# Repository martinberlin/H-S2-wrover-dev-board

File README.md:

## An open source S2-WROVER board with minimun components and DFU USB

H stands for Hardware. **IMPORTANT NOTE: Please do not intend to build this PCB. **
It was my first EPDiy like controller and has a lot of newbie defects. Including selecting no REAL TIME pins from the IO MUX to use as Clock and Start pulse for I2S. As is won't work, and in the next months, I won't have time to play with electronics.

Initial dimensions:
99x50mm

Note: Previews are taken from the [v1 branch](https://github.com/martinberlin/H-S2-wrover-dev-board/tree/v1).

This board aims to be the simplest possible configuration to have a breakout PCB to start developing something with Espressif S2.
The minimun requirements are:

- Lipo charger and a 2 leds indicator (charge, full)
- All GPIOs exposed
- No Serial-to-UART. Only dfu USB, please check this [blog post from Espressif](https://blog.espressif.com/dfu-using-the-native-usb-on-esp32-s2-for-flashing-the-firmware-b2c4af3335f1)
- Only 2 layer (Cheaper to fabricate)
- **Important** For simplicity this test board has no Auto-Reset circuit (Check [epdiy Schematic](https://github.com/martinberlin/H-S2-wrover-dev-board/tree/epd-v1/Schematic))

## EPDiy S2 PCB

In the **epd-v1** branch it's my first attempt to design an EPDiy V6 clone. This is still on fabrication and as the prototype Revision 1.1 still need a lot of tests and adjustments.
This will be probably merged in master once is tested and working as expected. Being my first somehow complex ESP32S2 boards I will for sure 

Both boards Still a work in progress, no Gerbers, no pick-place and no production files at all. It needs testing before everything can be published.

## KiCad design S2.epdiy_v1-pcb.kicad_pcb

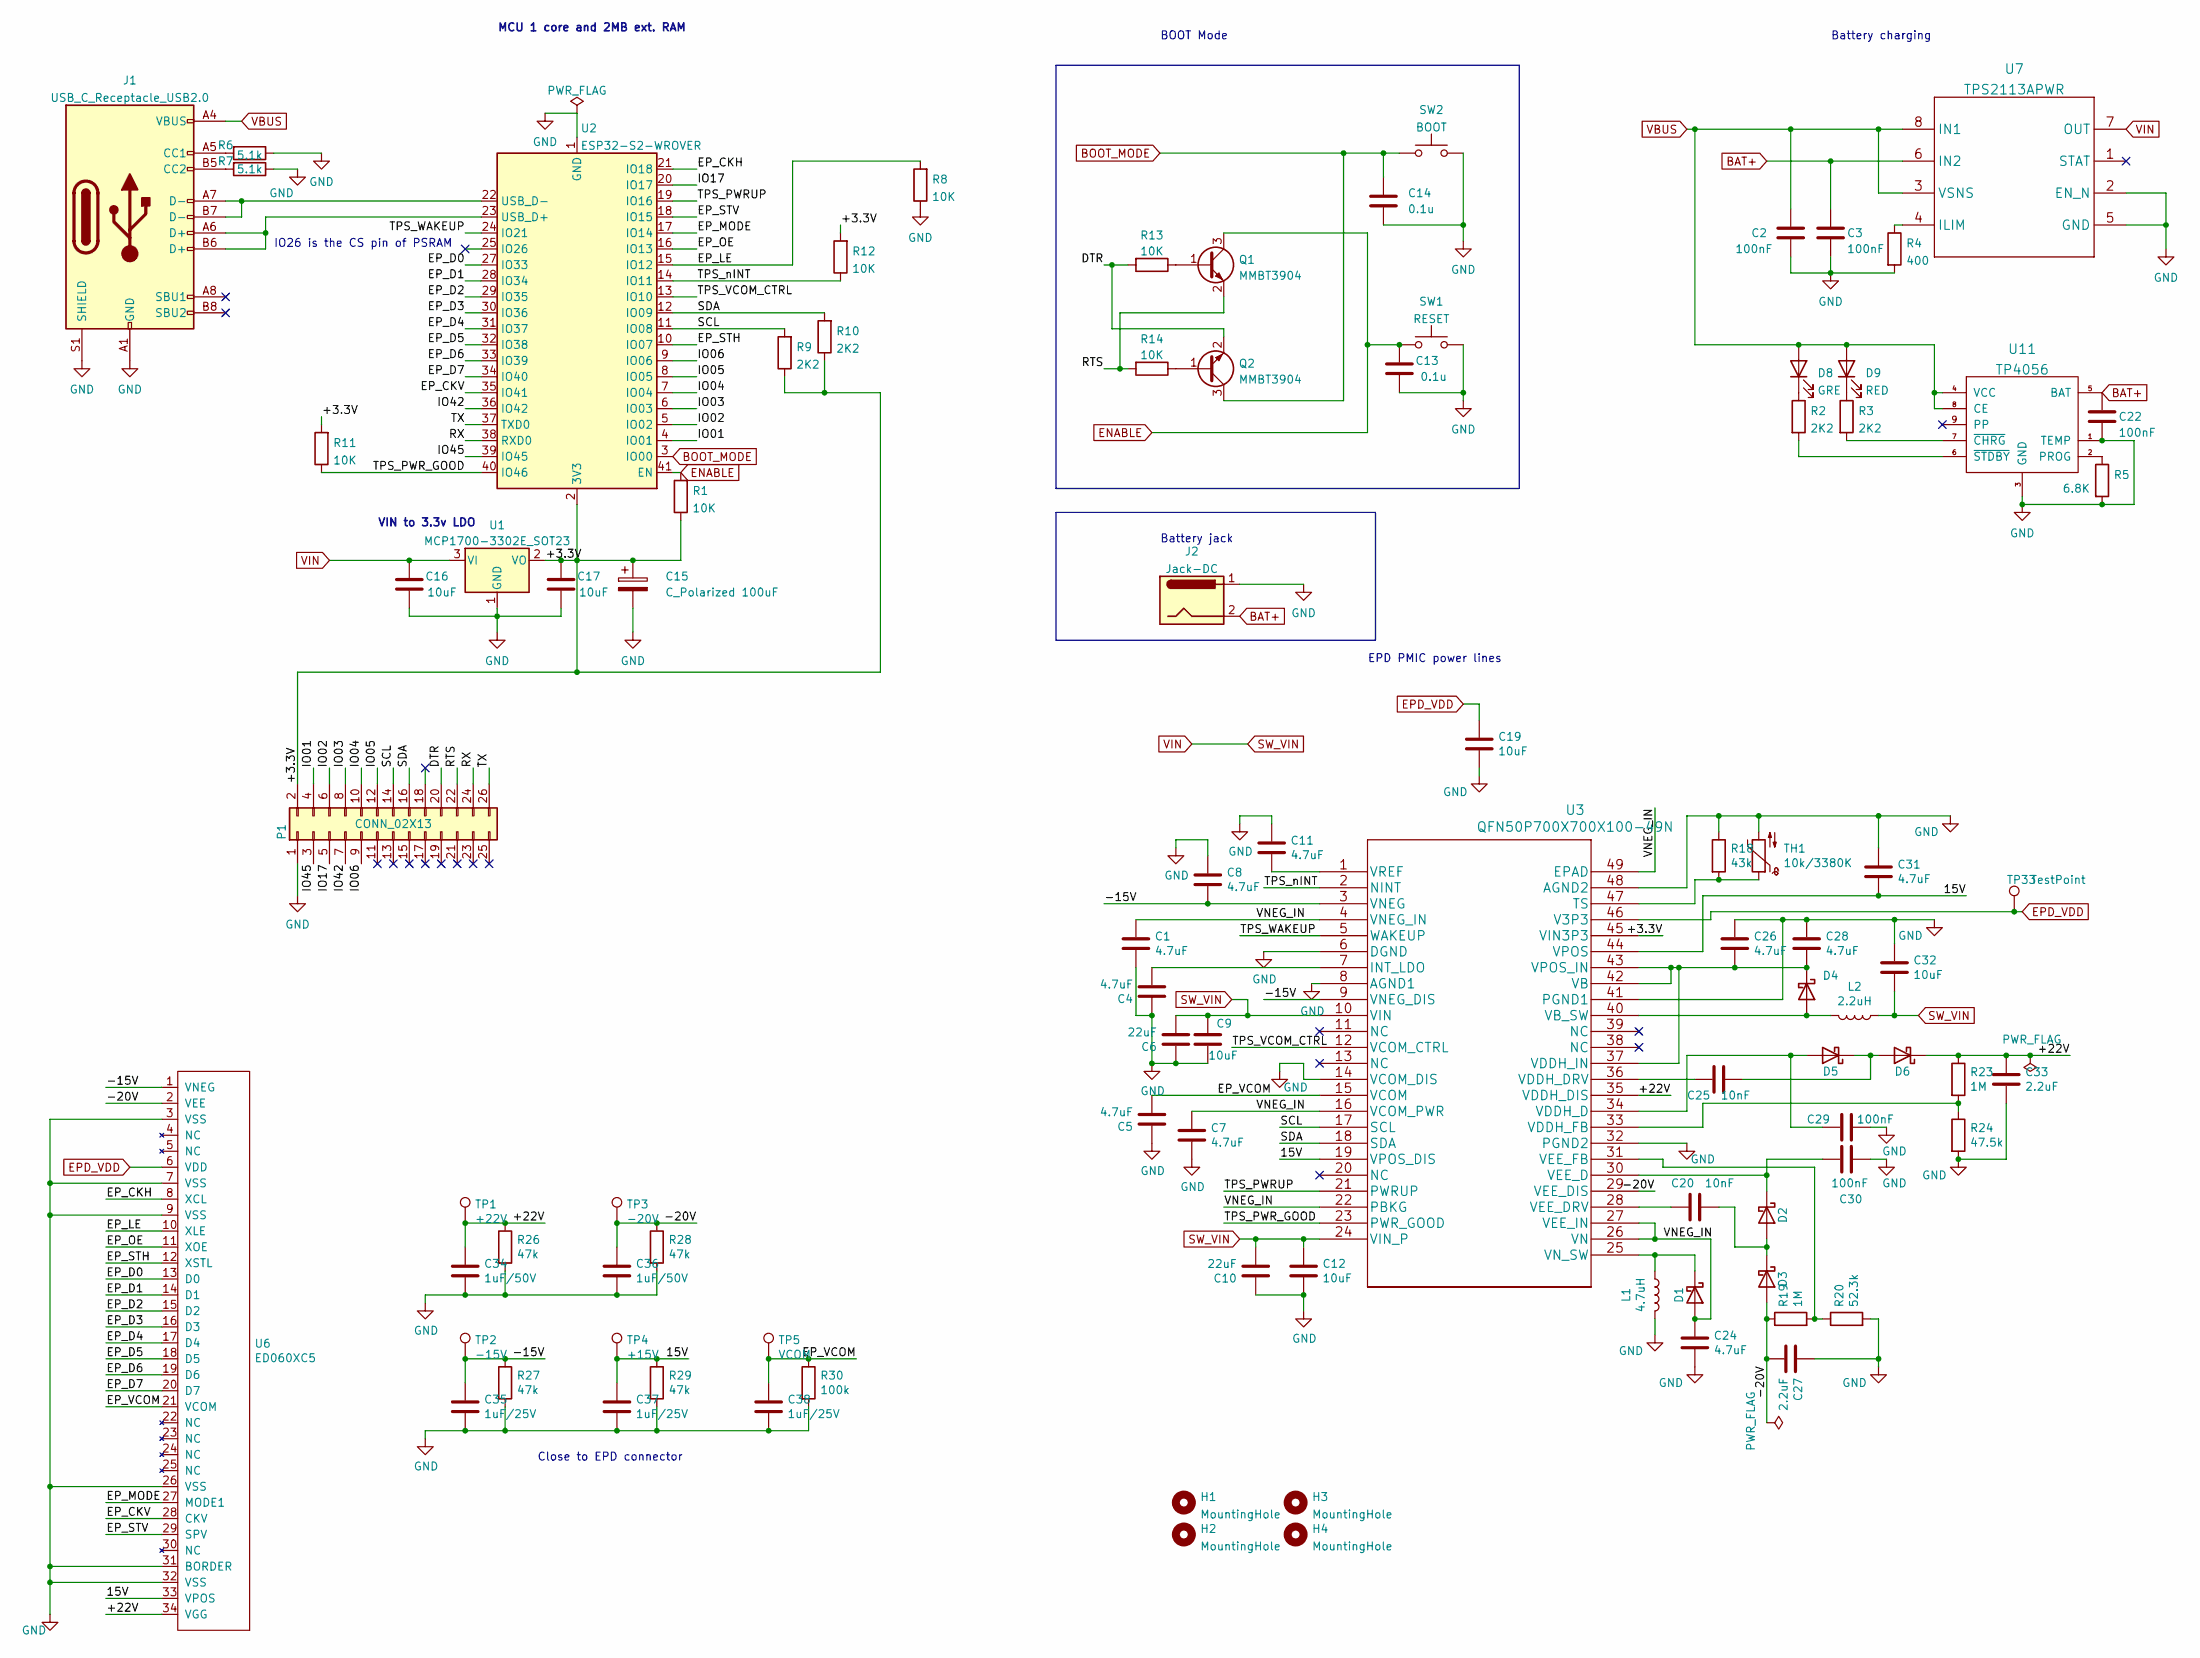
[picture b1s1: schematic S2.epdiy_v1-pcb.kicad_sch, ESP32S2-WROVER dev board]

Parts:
C1, C4, C5, C7, C8, C11, C24, C26, C28, C31: 4.7uF; C_0805_2012Metric; LCSC C1779
C2, C3, C22, C29, C30: 100nF; C_0805_2012Metric; LCSC C49678
C6, C10: 22uF; C_0805_2012Metric; LCSC C45783
C9, C12, C16, C17, C32: 10uF; C_0805_2012Metric; LCSC C15850
C13: 0.1u; C_0805_2012Metric
C14: 0.1u; C_0805_2012Metric; LCSC C28323
C15: C_Polarized 100uF; CP_EIA-3528-21_Kemet-B; LCSC C129289
C19: 10uF; C_0805_2012Metric; LCSC C19702
C20, C25: 10nF; C_0805_2012Metric; LCSC C1710
C27, C33: 2.2uF; C_0805_2012Metric; LCSC C49217
C34, C36: 1uF/50V; C_1206_3216Metric; LCSC C1848
C35, C37, C38: 1uF/25V; C_0805_2012Metric; LCSC C28323
D1, D2, D3, D4, D5, D6: MBR0540; D_SOD-123; LCSC C21353
D8: GRE; LED_0805_2012Metric; LCSC C2297
D9: RED; LED_0805_2012Metric; LCSC C84256
H1, H2, H3, H4: MountingHole; MountingHole_2.5mm
J1: USB_C_Receptacle_USB2.0; USB_C_Receptacle_HRO_TYPE-C-31-M-12; LCSC C165948
J2: Jack-DC; JST_EH_S2B-EH_1x02_P2.50mm_Horizontal
L1: 4.7uH; L_Taiyo-Yuden_NR-50xx_HandSoldering; LCSC C222947
L2: 2.2uH; L_Taiyo-Yuden_NR-40xx_HandSoldering; LCSC C92959
P1: CONN_02X13; PinHeader_2x13_P2.54mm_Vertical
Q1, Q2: MMBT3904; SOT-23; LCSC C20526
R1, R8, R11, R13: 10K; R_0603_1608Metric; LCSC C25804
R2, R3: 2K2; R_0603_1608Metric; LCSC C25804
R4: 400; R_0603_1608Metric; LCSC C23151
R5: 6.8K; R_0603_1608Metric; LCSC C23212
R6, R7: 5.1k; R_0603_1608Metric; LCSC C25803
R9, R10: 2K2; R_0603_1608Metric; LCSC C4190
R12, R14: 10K; R_0603_1608Metric; LCSC C25197
R18: 43k; R_0603_1608Metric; LCSC C23172
R19, R23: 1M; R_0603_1608Metric; LCSC C22935
R20: 52.3k; R_0603_1608Metric; LCSC C23196
R24: 47.5k; R_0603_1608Metric; LCSC C25819
R26, R27, R28, R29: 47k; R_0603_1608Metric; LCSC C25819
R30: 100k; R_0603_1608Metric; LCSC C25803
SW1: RESET; Alps_SKRK
SW2: BOOT; Alps_SKRK; LCSC C202388
TH1: 10k/3380K; R_0603_1608Metric; LCSC C76589
TP1: +22V; TestPoint_Pad_D2.5mm
TP2: -15V; TestPoint_Pad_D2.5mm
TP3: -20V; TestPoint_Pad_D2.5mm
TP4: +15V; TestPoint_Pad_D2.5mm
TP5: VCOM; TestPoint_Pad_D2.5mm
TP33: TestPoint; TestPoint_Pad_2.0x2.0mm
U1: MCP1700-3302E_SOT23; SOT-23; LCSC C39051
U2: ESP32-S2-WROVER; LCSC C701333
U3: QFN50P700X700X100-49N; TPS65185RGZR_700X700X100-49N; LCSC C139292
U6: ED060XC5; X05A20H34G; LCSC C528053
U7: TPS2113APWR; TPS2113APW; LCSC C130052
U11: TP4056; TP4056_SOP-8-PP; LCSC C16581

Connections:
/15V: C31.2, C37.1, R29.1, TP4.1, U3.19 (VPOS_DIS), U3.44 (VPOS), U6.33 (VPOS)
/+3.3V: C15.1, C17.1, P1.2, R1.1, R9.1, R10.1, R11.2, R12.2, U1.2 (VO), U2.2 (3V3), U3.45 (VIN3P3)
/+22V: C33.1, C34.1, D6.1 (K), R23.1, R26.1, TP1.1, U3.35 (VDDH_DIS), U6.34 (VGG)
/-15V: C8.2, C35.1, R27.1, TP2.1, U3.3 (VNEG), U3.9 (VNEG_DIS), U6.1 (VNEG)
/-20V: C27.2, C36.1, D3.2 (A), R19.1, R28.1, TP3.1, U3.29 (VEE_DIS), U6.2 (VEE)
/DTR: P1.20, Q2.2 (E), R13.2
/EP_CKH: U2.21 (IO18), U6.8 (XCL)
/EP_CKV: U2.35 (IO41), U6.28 (CKV)
/EP_D0: U2.27 (IO33), U6.13 (D0)
/EP_D1: U2.28 (IO34), U6.14 (D1)
/EP_D2: U2.29 (IO35), U6.15 (D2)
/EP_D3: U2.30 (IO36), U6.16 (D3)
/EP_D4: U2.31 (IO37), U6.17 (D4)
/EP_D5: U2.32 (IO38), U6.18 (D5)
/EP_D6: U2.33 (IO39), U6.19 (D6)
/EP_D7: U2.34 (IO40), U6.20 (D7)
/EP_LE: R8.2, U2.15 (IO12), U6.10 (XLE)
/EP_MODE: U2.17 (IO14), U6.27 (MODE1)
/EP_OE: U2.16 (IO13), U6.11 (XOE)
/EP_STH: U2.10 (IO07), U6.12 (XSTL)
/EP_STV: U2.18 (IO15), U6.29 (SPV)
/EP_VCOM: C5.2, C38.1, R30.1, TP5.1, U3.15 (VCOM), U6.21 (VCOM)
/IO01: P1.4, U2.4 (IO01)
/IO02: P1.6, U2.5 (IO02)
/IO03: P1.8, U2.6 (IO03)
/IO04: P1.10, U2.7 (IO04)
/IO05: P1.12, U2.8 (IO05)
/IO06: P1.9, U2.9 (IO06)
/IO17: P1.5, U2.20 (IO17)
/IO42: P1.7, U2.36 (IO42)
/IO45: P1.3, U2.39 (IO45)
/RTS: P1.22, Q1.2 (E), R14.2
/RX: P1.24, U2.38 (RXD0)
/SCL: P1.14, R9.2, U2.11 (IO08), U3.17 (SCL)
/SDA: P1.16, R10.2, U2.12 (IO09), U3.18 (SDA)
/TPS_PWRUP: U2.19 (IO16), U3.21 (PWRUP)
/TPS_PWR_GOOD: R11.1, U2.40 (IO46), U3.23 (PWR_GOOD)
/TPS_VCOM_CTRL: U2.13 (IO10), U3.12 (VCOM_CTRL)
/TPS_WAKEUP: U2.24 (IO21), U3.5 (WAKEUP)
/TPS_nINT: R12.1, U2.14 (IO11), U3.2 (NINT)
/TX: P1.26, U2.37 (TXD0)
/VNEG_IN: C1.1, C7.1, C24.1, D1.2 (A), U3.4 (VNEG_IN), U3.16 (VCOM_PWR), U3.22 (PBKG), U3.26 (VN), U3.27 (VEE_IN), U3.49 (EPAD)
BAT+: C3.2, C22.2, J2.2, U7.6 (IN2), U11.5 (BAT)
BOOT_MODE: C14.2, Q2.3 (C), SW2.1, U2.3 (IO00)
ENABLE: C13.1, Q1.3 (C), R1.2, SW1.1, U2.41 (EN)
EPD_VDD: C19.1, TP33.1, U3.46 (V3P3), U6.6 (VDD)
GND: C1.2, C2.1, C3.1, C4.1, C5.1, C6.1, C7.2, C8.1, C9.2, C10.1, C11.1, C12.2, C13.2, C14.1, C15.2, C16.2, C17.2, C19.2, C22.1, C24.2, C26.1, C27.1, C28.1, C29.1, C30.2, C31.1, C32.1, C33.2, C34.2, C35.2, C36.2, C37.2, C38.2, J1.A1 (GND), J1.A12 (GND), J1.B1 (GND), J1.B12 (GND), J1.S1 (SHIELD), J2.1, L1.2, P1.1, R4.2, R5.2, R6.1, R7.1, R8.1, R18.1, R20.2, R24.2, R26.2, R27.2, R28.2, R29.2, R30.2, SW1.2, SW2.2, TH1.2, U1.1 (GND), U2.1 (GND), U2.26 (GND), U2.42 (GND), U2.43 (GND), U3.6 (DGND), U3.8 (AGND1), U3.14 (VCOM_DIS), U3.32 (PGND2), U3.41 (PGND1), U3.48 (AGND2), U6.3 (VSS), U6.7 (VSS), U6.9 (VSS), U6.26 (VSS), U6.31 (BORDER), U6.32 (VSS), U7.2 (EN_N), U7.5 (GND), U11.1 (TEMP), U11.3 (GND)
unnamed: C4.2, U3.7 (INT_LDO)
unnamed: C11.2, U3.1 (VREF)
unnamed: C20.1, D2.2 (A), D3.1 (K)
unnamed: C20.2, U3.28 (VEE_DRV)
unnamed: C25.1, D5.1 (K), D6.2 (A)
unnamed: C25.2, U3.36 (VDDH_DRV)
unnamed: C26.2, C28.2, D4.1 (K), U3.37 (VDDH_IN), U3.42 (VB), U3.43 (VPOS_IN)
unnamed: C29.2, D5.2 (A), U3.34 (VDDH_D)
unnamed: C30.1, D2.1 (K), U3.30 (VEE_D)
unnamed: D1.1 (K), L1.1, U3.25 (VN_SW)
unnamed: D4.2 (A), L2.2, U3.40 (VB_SW)
unnamed: D8.1 (K), R2.1
unnamed: D9.1 (K), R3.1
unnamed: J1.A5 (CC1), R6.2
unnamed: J1.A6 (D+), J1.B6 (D+), U2.23 (USB_D+)
unnamed: J1.A7 (D-), J1.B7 (D-), U2.22 (USB_D-)
unnamed: J1.B5 (CC2), R7.2
unnamed: Q1.1 (B), R13.1
unnamed: Q2.1 (B), R14.1
unnamed: R2.2, U11.6 (~STDBY)
unnamed: R3.2, U11.7 (~CHRG)
unnamed: R4.1, U7.4 (ILIM)
unnamed: R5.1, U11.2 (PROG)
unnamed: R18.2, TH1.1, U3.47 (TS)
unnamed: R19.2, R20.1, U3.31 (VEE_FB)
unnamed: R23.2, R24.1, U3.33 (VDDH_FB)
SW_VIN: C6.2, C9.1, C10.2, C12.1, C16.1, C32.2, L2.1, U1.3 (VI), U3.10 (VIN), U3.24 (VIN_P), U7.7 (OUT)
VBUS: C2.2, D8.2 (A), D9.2 (A), J1.A4 (VBUS), J1.A9 (VBUS), J1.B4 (VBUS), J1.B9 (VBUS), U7.3 (VSNS), U7.8 (IN1), U11.4 (VCC), U11.8 (CE)

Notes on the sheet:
Battery charging
Battery jack
Close to EPD connector
BOOT Mode
MCU 1 core and 2MB ext. RAM
IO26 is the CS pin of PSRAM
EPD PMIC power lines
VIN to 3.3v LDO

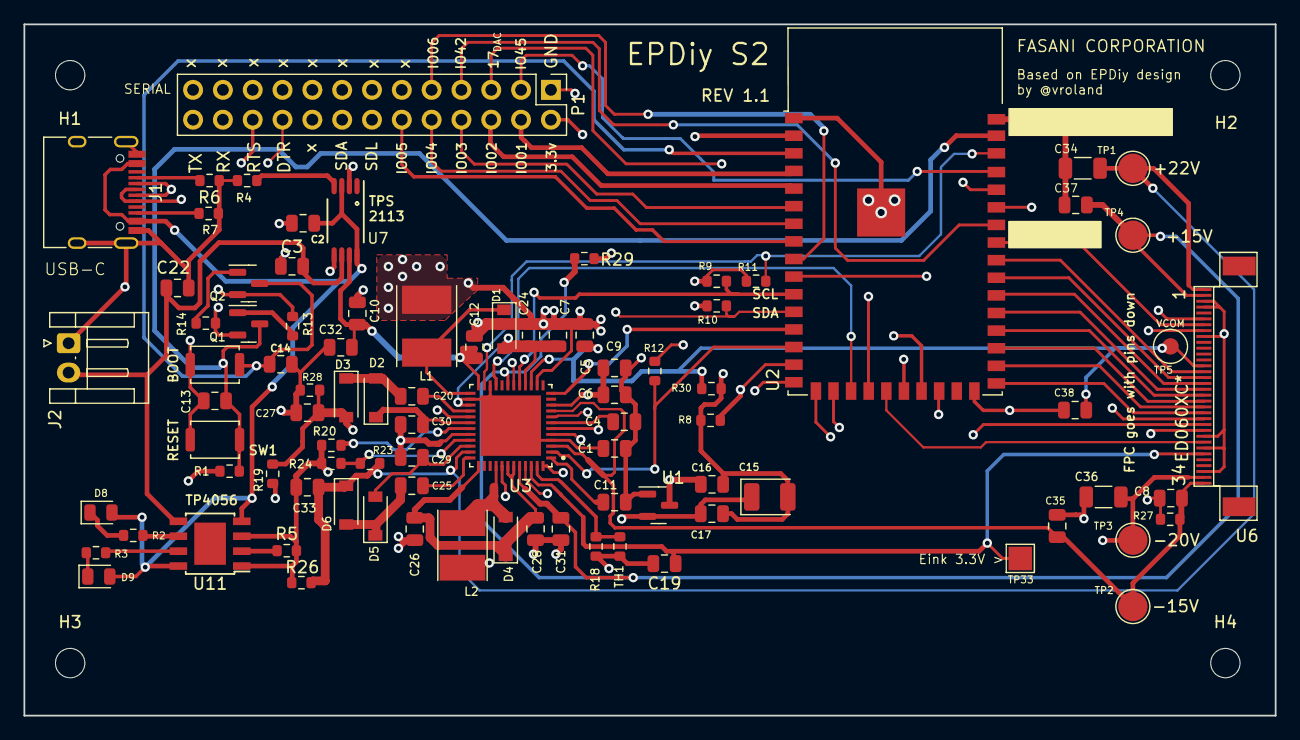
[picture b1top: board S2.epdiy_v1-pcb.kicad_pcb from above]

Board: 4 copper layers, 106.6 x 58.9 mm, 93 parts (0 on the bottom side), 75 nets.

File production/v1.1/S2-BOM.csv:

"Id";"Designator";"Package";"Quantity";"Designation";"Supplier and ref";
1;"R14,R13,R12,R8,R11,R1";"R_0603_1608Metric";6;"10K";;;
2;"Q2,Q1";"SOT-23";2;"MMBT3904";;;
3;"C15";"CP_EIA-3528-21_Kemet-B";1;"C_Polarized 100uF";;;
4;"C34,C36";"C_1206_3216Metric";2;"1uF/50V";;;
5;"D8";"LED_0805_2012Metric";1;"GRE";;;
6;"C31,C5,C24,C1,C26,C28,C11,C7,C8,C4";"C_0805_2012Metric";10;"4.7uF";;;
7;"U7";"TPS2113APW";1;"TPS2113APWR";;;
8;"TP33";"TestPoint_Pad_2.0x2.0mm";1;"TestPoint";;;
9;"R10,R3,R2,R9";"R_0603_1608Metric";4;"2K2";;;
10;"TP1";"TestPoint_Pad_D2.5mm";1;"+22V";;;
11;"C16,C9,C12,C19,C32,C17";"C_0805_2012Metric";6;"10uF";;;
12;"SW2";"Alps_SKRK";1;"BOOT";;;
13;"R5";"R_0603_1608Metric";1;"6.8K";;;
14;"C10,C6";"C_0805_2012Metric";2;"22uF";;;
15;"D2,D1,D3,D4,D6,D5";"D_SOD-123";6;"MBR0540";;;
16;"C3,C22,C29,C2,C30";"C_0805_2012Metric";5;"100nF";;;
17;"R24";"R_0603_1608Metric";1;"47.5k";;;
18;"C14,C13";"C_0805_2012Metric";2;"0.1u";;;
19;"TP3";"TestPoint_Pad_D2.5mm";1;"-20V";;;
20;"R30";"R_0603_1608Metric";1;"100k";;;
21;"H1,H3,H4,H2";"MountingHole_2.5mm";4;"MountingHole";;;
22;"R4";"R_0603_1608Metric";1;"400";;;
23;"R20";"R_0603_1608Metric";1;"52.3k";;;
24;"R19,R23";"R_0603_1608Metric";2;"1M";;;
25;"U3";"TPS65185RGZR_700X700X100-49N";1;"QFN50P700X700X100-49N";;;
26;"C27,C33";"C_0805_2012Metric";2;"2.2uF";;;
27;"C20,C25";"C_0805_2012Metric";2;"10nF";;;
28;"J2";"JST_EH_S2B-EH_1x02_P2.50mm_Horizontal";1;"Jack-DC";;;
29;"R28,R29,R27,R26";"R_0603_1608Metric";4;"47k";;;
30;"L1";"L_Taiyo-Yuden_NR-50xx_HandSoldering";1;"4.7uH";;;
31;"TP4";"TestPoint_Pad_D2.5mm";1;"+15V";;;
32;"R7,R6";"R_0603_1608Metric";2;"5.1k";;;
33;"U6";"X05A20H34G";1;"ED060XC5";;;
34;"C38,C35,C37";"C_0805_2012Metric";3;"1uF/25V";;;
35;"R18";"R_0603_1608Metric";1;"43k";;;
36;"U2";"ESP32-S2-WROVER";1;"ESP32-S2-WROVER";;;
37;"TH1";"R_0603_1608Metric";1;"10k/3380K";;;
38;"P1";"PinHeader_2x13_P2.54mm_Vertical";1;"CONN_02X13";;;
39;"U1";"SOT-23";1;"MCP1700-3302E_SOT23";;;
40;"D9";"LED_0805_2012Metric";1;"RED";;;
41;"U11";"TP4056_SOP-8-PP";1;"TP4056";;;
42;"SW1";"Alps_SKRK";1;"RESET";;;
43;"J1";"USB_C_Receptacle_HRO_TYPE-C-31-M-12";1;"USB_C_Receptacle_USB2.0";;;
44;"L2";"L_Taiyo-Yuden_NR-40xx_HandSoldering";1;"2.2uH";;;
45;"TP5";"TestPoint_Pad_D2.5mm";1;"VCOM";;;
46;"TP2";"TestPoint_Pad_D2.5mm";1;"-15V";;;

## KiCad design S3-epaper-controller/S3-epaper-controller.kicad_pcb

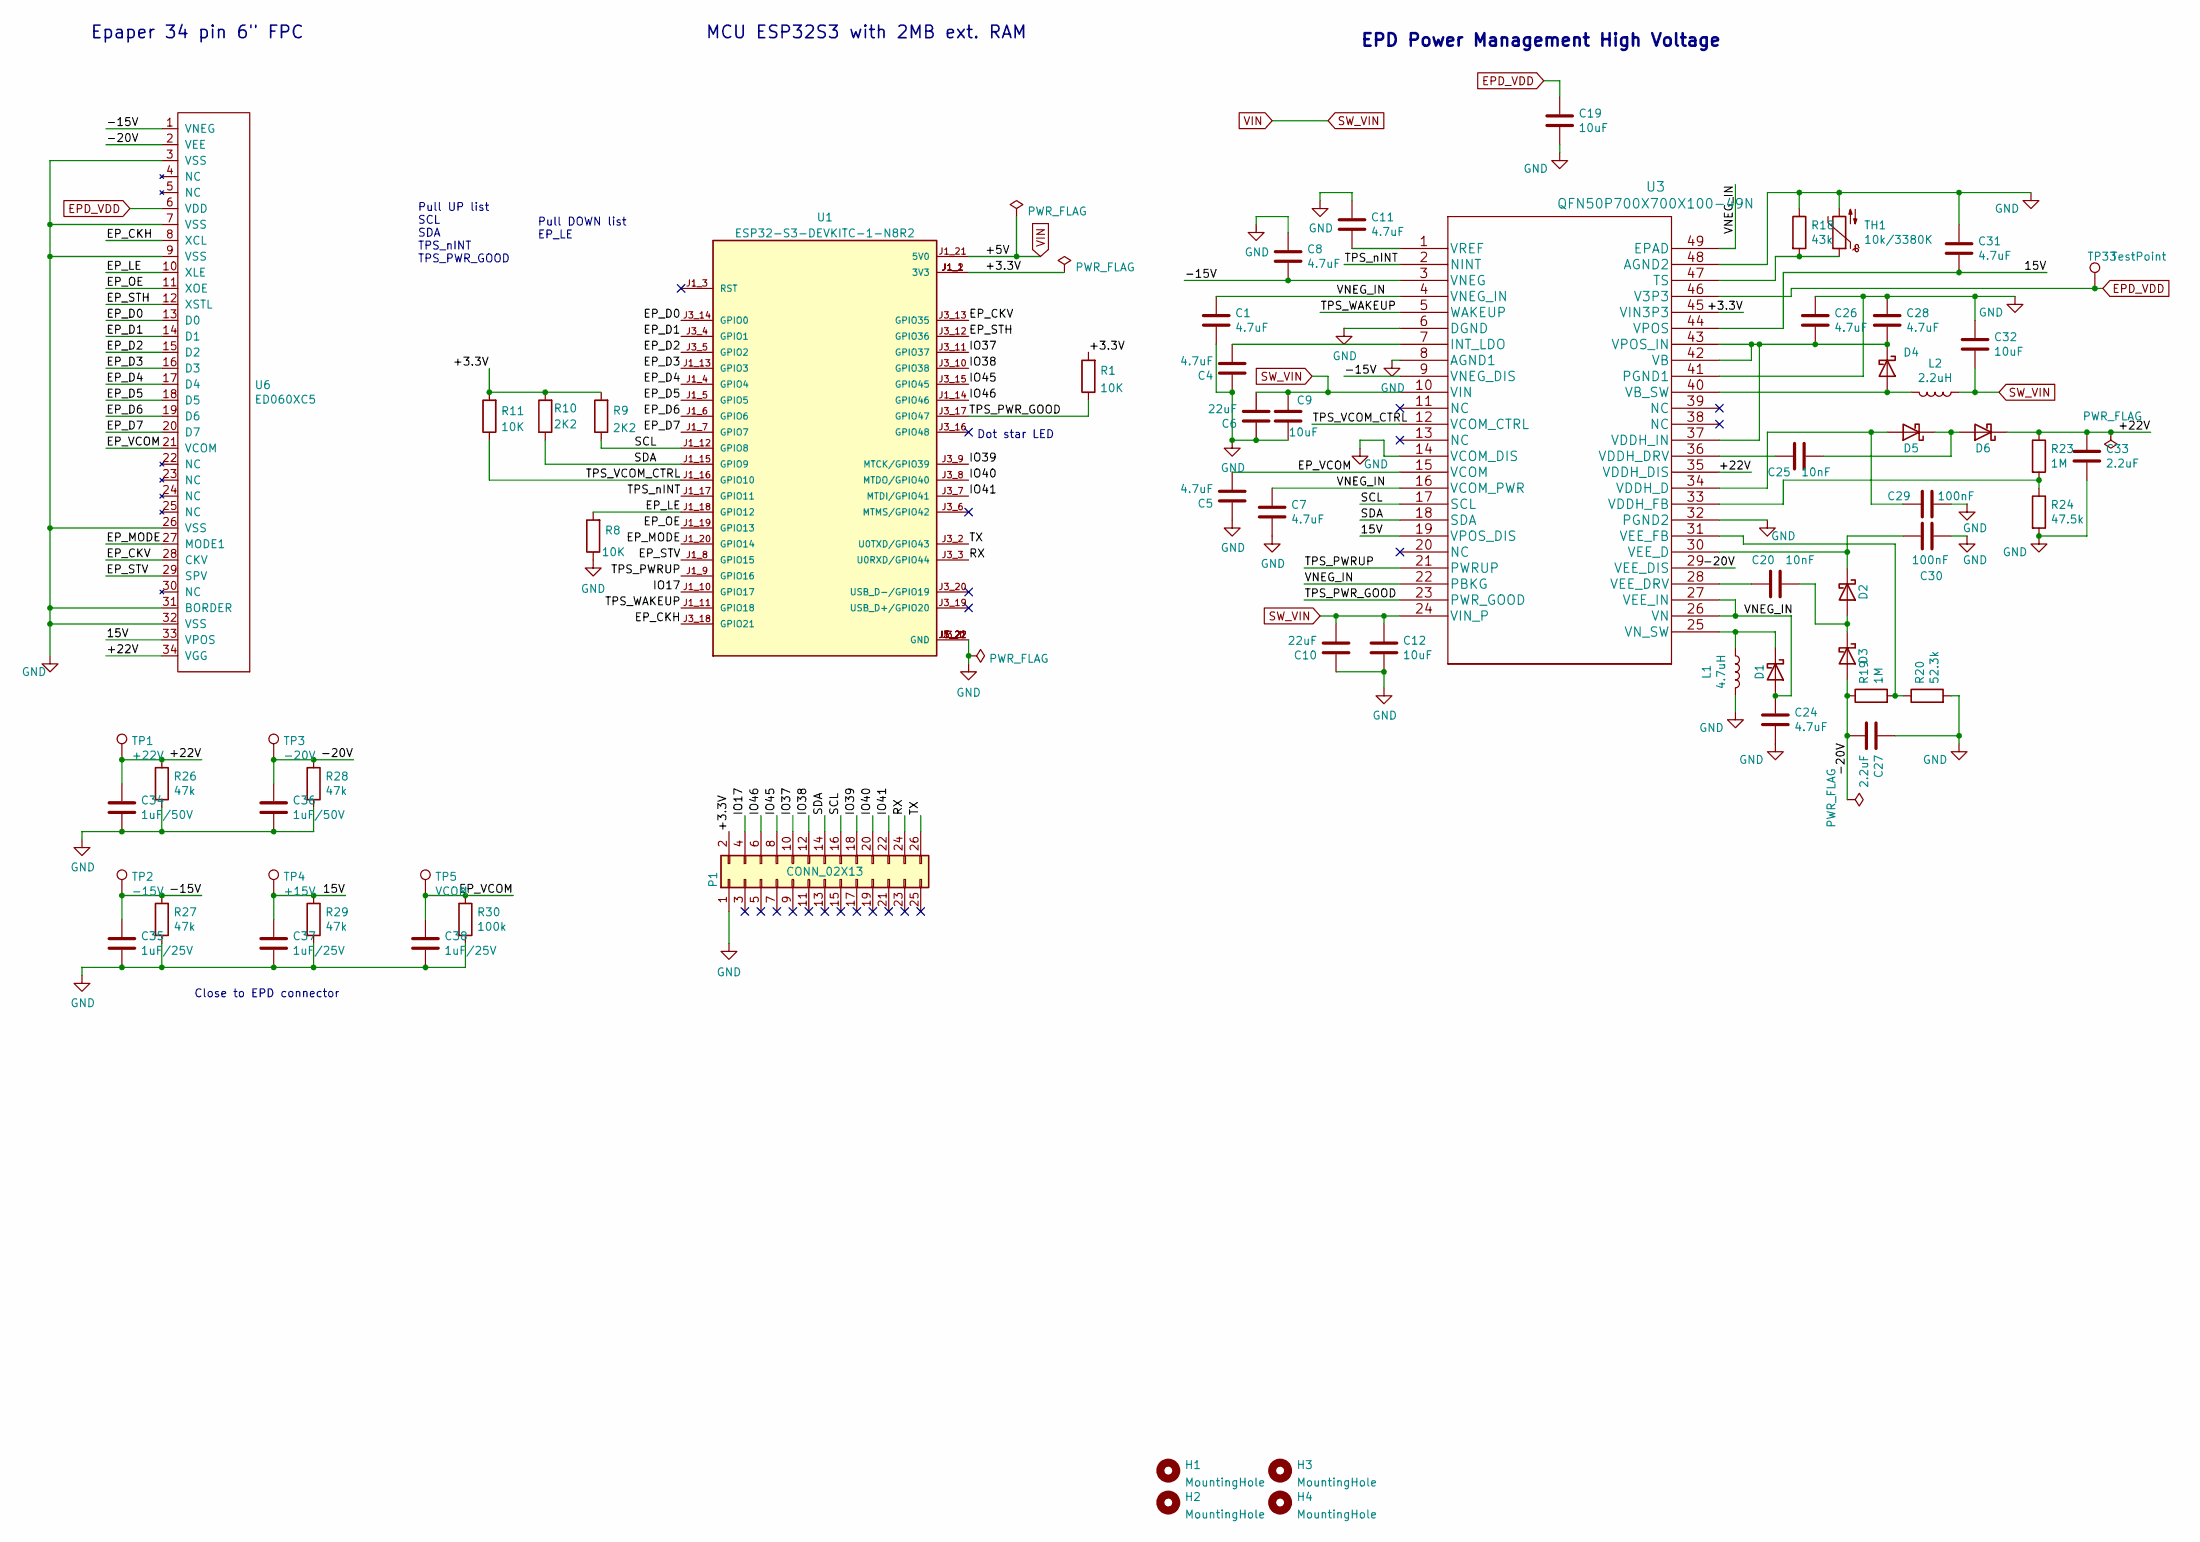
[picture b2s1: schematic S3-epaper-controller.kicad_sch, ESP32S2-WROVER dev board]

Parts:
C1, C4, C5, C7, C8, C11, C24, C26, C28, C31: 4.7uF; C_0805_2012Metric; LCSC C1779
C6, C10: 22uF; C_0805_2012Metric; LCSC C45783
C9, C12, C32: 10uF; C_0805_2012Metric; LCSC C15850
C19: 10uF; C_0805_2012Metric; LCSC C19702
C20, C25: 10nF; C_0805_2012Metric; LCSC C1710
C27, C33: 2.2uF; C_0805_2012Metric; LCSC C49217
C29, C30: 100nF; C_0805_2012Metric; LCSC C49678
C34, C36: 1uF/50V; C_1206_3216Metric; LCSC C1848
C35, C37, C38: 1uF/25V; C_0805_2012Metric; LCSC C28323
D1, D2, D3, D4, D5, D6: MBR0540; D_SOD-123; LCSC C21353
H1, H2, H3, H4: MountingHole; MountingHole_2.5mm
L1: 4.7uH; L_Taiyo-Yuden_NR-50xx_HandSoldering; LCSC C222947
L2: 2.2uH; L_Taiyo-Yuden_NR-40xx_HandSoldering; LCSC C92959
P1: CONN_02X13; PinHeader_2x13_P2.54mm_Vertical
R1, R8, R11: 10K; R_0603_1608Metric; LCSC C25197
R9, R10: 2K2; R_0603_1608Metric; LCSC C4190
R18: 43k; R_0603_1608Metric; LCSC C23172
R19, R23: 1M; R_0603_1608Metric; LCSC C22935
R20: 52.3k; R_0603_1608Metric; LCSC C23196
R24: 47.5k; R_0603_1608Metric; LCSC C25819
R26, R27, R28, R29: 47k; R_0603_1608Metric; LCSC C25819
R30: 100k; R_0603_1608Metric; LCSC C25803
TH1: 10k/3380K; R_0603_1608Metric; LCSC C76589
TP1: +22V; TestPoint_Pad_D2.5mm
TP2: -15V; TestPoint_Pad_D2.5mm
TP3: -20V; TestPoint_Pad_D2.5mm
TP4: +15V; TestPoint_Pad_D2.5mm
TP5: VCOM; TestPoint_Pad_D2.5mm
TP33: TestPoint; TestPoint_Pad_2.0x2.0mm
U1: ESP32-S3-DEVKITC-1-N8R2; PARTREV V1
U3: QFN50P700X700X100-49N; TPS65185RGZR_700X700X100-49N; LCSC C139292
U6: ED060XC5; X05A20H34G; LCSC C528053

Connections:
/15V: C31.2, C37.1, R29.1, TP4.1, U3.19 (VPOS_DIS), U3.44 (VPOS), U6.33 (VPOS)
/+3.3V: P1.2, R1.2, R9.2, R10.2, R11.2, U1.J1_1 (3V3), U1.J1_2 (3V3), U3.45 (VIN3P3)
/+22V: C33.1, C34.1, D6.1 (K), R23.1, R26.1, TP1.1, U3.35 (VDDH_DIS), U6.34 (VGG)
/-15V: C8.2, C35.1, R27.1, TP2.1, U3.3 (VNEG), U3.9 (VNEG_DIS), U6.1 (VNEG)
/-20V: C27.2, C36.1, D3.2 (A), R19.1, R28.1, TP3.1, U3.29 (VEE_DIS), U6.2 (VEE)
/EP_CKH: U1.J3_18 (GPIO21), U6.8 (XCL)
/EP_CKV: U1.J3_13 (GPIO35), U6.28 (CKV)
/EP_D0: U1.J3_14 (GPIO0), U6.13 (D0)
/EP_D1: U1.J3_4 (GPIO1), U6.14 (D1)
/EP_D2: U1.J3_5 (GPIO2), U6.15 (D2)
/EP_D3: U1.J1_13 (GPIO3), U6.16 (D3)
/EP_D4: U1.J1_4 (GPIO4), U6.17 (D4)
/EP_D5: U1.J1_5 (GPIO5), U6.18 (D5)
/EP_D6: U1.J1_6 (GPIO6), U6.19 (D6)
/EP_D7: U1.J1_7 (GPIO7), U6.20 (D7)
/EP_LE: R8.2, U1.J1_18 (GPIO12), U6.10 (XLE)
/EP_MODE: U1.J1_20 (GPIO14), U6.27 (MODE1)
/EP_OE: U1.J1_19 (GPIO13), U6.11 (XOE)
/EP_STH: U1.J3_12 (GPIO36), U6.12 (XSTL)
/EP_STV: U1.J1_8 (GPIO15), U6.29 (SPV)
/EP_VCOM: C5.2, C38.1, R30.1, TP5.1, U3.15 (VCOM), U6.21 (VCOM)
/IO17: P1.4, U1.J1_10 (GPIO17)
/IO37: P1.10, U1.J3_11 (GPIO37)
/IO38: P1.12, U1.J3_10 (GPIO38)
/IO39: P1.18, U1.J3_9 (MTCK/GPIO39)
/IO40: P1.20, U1.J3_8 (MTDO/GPIO40)
/IO41: P1.22, U1.J3_7 (MTDI/GPIO41)
/IO45: P1.8, U1.J3_15 (GPIO45)
/IO46: P1.6, U1.J1_14 (GPIO46)
/RX: P1.24, U1.J3_3 (U0RXD/GPIO44)
/SCL: P1.16, R9.1, U1.J1_12 (GPIO8), U3.17 (SCL)
/SDA: P1.14, R10.1, U1.J1_15 (GPIO9), U3.18 (SDA)
/TPS_PWRUP: U1.J1_9 (GPIO16), U3.21 (PWRUP)
/TPS_PWR_GOOD: R1.1, U1.J3_17 (GPIO47), U3.23 (PWR_GOOD)
/TPS_VCOM_CTRL: R11.1, U1.J1_16 (GPIO10), U3.12 (VCOM_CTRL)
/TPS_WAKEUP: U1.J1_11 (GPIO18), U3.5 (WAKEUP)
/TPS_nINT: U1.J1_17 (GPIO11), U3.2 (NINT)
/TX: P1.26, U1.J3_2 (U0TXD/GPIO43)
/VNEG_IN: C1.1, C7.1, C24.1, D1.2 (A), U3.4 (VNEG_IN), U3.16 (VCOM_PWR), U3.22 (PBKG), U3.26 (VN), U3.27 (VEE_IN), U3.49 (EPAD)
EPD_VDD: C19.1, TP33.1, U3.46 (V3P3), U6.6 (VDD)
GND: C1.2, C4.1, C5.1, C6.1, C7.2, C8.1, C9.2, C10.1, C11.1, C12.2, C19.2, C24.2, C26.1, C27.1, C28.1, C29.1, C30.2, C31.1, C32.1, C33.2, C34.2, C35.2, C36.2, C37.2, C38.2, L1.2, P1.1, R8.1, R18.1, R20.2, R24.2, R26.2, R27.2, R28.2, R29.2, R30.2, TH1.2, U1.J1_22 (GND), U1.J3_1 (GND), U1.J3_21 (GND), U1.J3_22 (GND), U3.6 (DGND), U3.8 (AGND1), U3.14 (VCOM_DIS), U3.32 (PGND2), U3.41 (PGND1), U3.48 (AGND2), U6.3 (VSS), U6.7 (VSS), U6.9 (VSS), U6.26 (VSS), U6.31 (BORDER), U6.32 (VSS)
unnamed: C4.2, U3.7 (INT_LDO)
unnamed: C11.2, U3.1 (VREF)
unnamed: C20.1, D2.2 (A), D3.1 (K)
unnamed: C20.2, U3.28 (VEE_DRV)
unnamed: C25.1, D5.1 (K), D6.2 (A)
unnamed: C25.2, U3.36 (VDDH_DRV)
unnamed: C26.2, C28.2, D4.1 (K), U3.37 (VDDH_IN), U3.42 (VB), U3.43 (VPOS_IN)
unnamed: C29.2, D5.2 (A), U3.34 (VDDH_D)
unnamed: C30.1, D2.1 (K), U3.30 (VEE_D)
unnamed: D1.1 (K), L1.1, U3.25 (VN_SW)
unnamed: D4.2 (A), L2.2, U3.40 (VB_SW)
unnamed: R18.2, TH1.1, U3.47 (TS)
unnamed: R19.2, R20.1, U3.31 (VEE_FB)
unnamed: R23.2, R24.1, U3.33 (VDDH_FB)
SW_VIN: C6.2, C9.1, C10.2, C12.1, C32.2, L2.1, U1.J1_21 (5V0), U3.10 (VIN), U3.24 (VIN_P)

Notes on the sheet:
Close to EPD connector
Pull UP list SCL SDA TPS_nINT TPS_PWR_GOOD
MCU ESP32S3 with 2MB ext. RAM
Dot star LED
EPD Power Management High Voltage
Pull DOWN list EP_LE
Epaper 34 pin 6" FPC

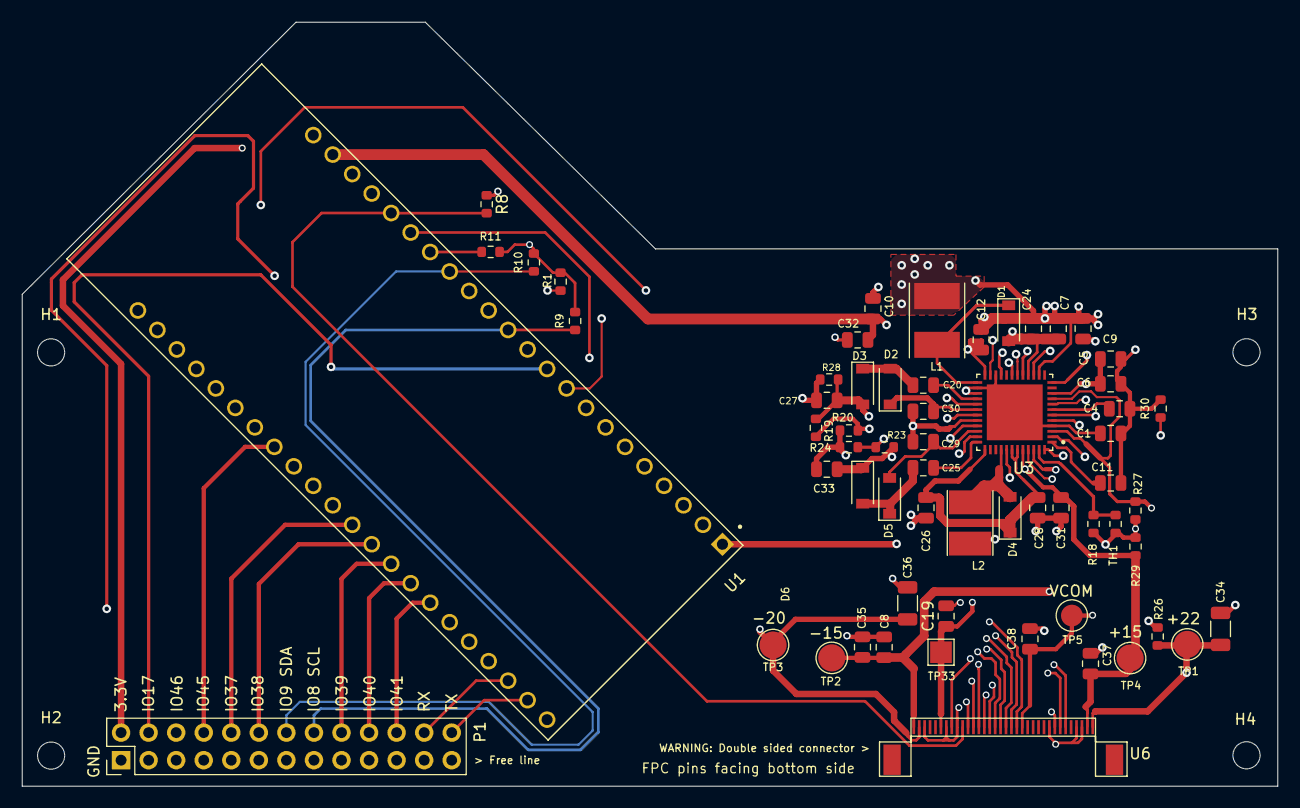
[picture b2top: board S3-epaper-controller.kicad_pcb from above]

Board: 4 copper layers, 115.7 x 70.4 mm, 65 parts (0 on the bottom side), 56 nets.

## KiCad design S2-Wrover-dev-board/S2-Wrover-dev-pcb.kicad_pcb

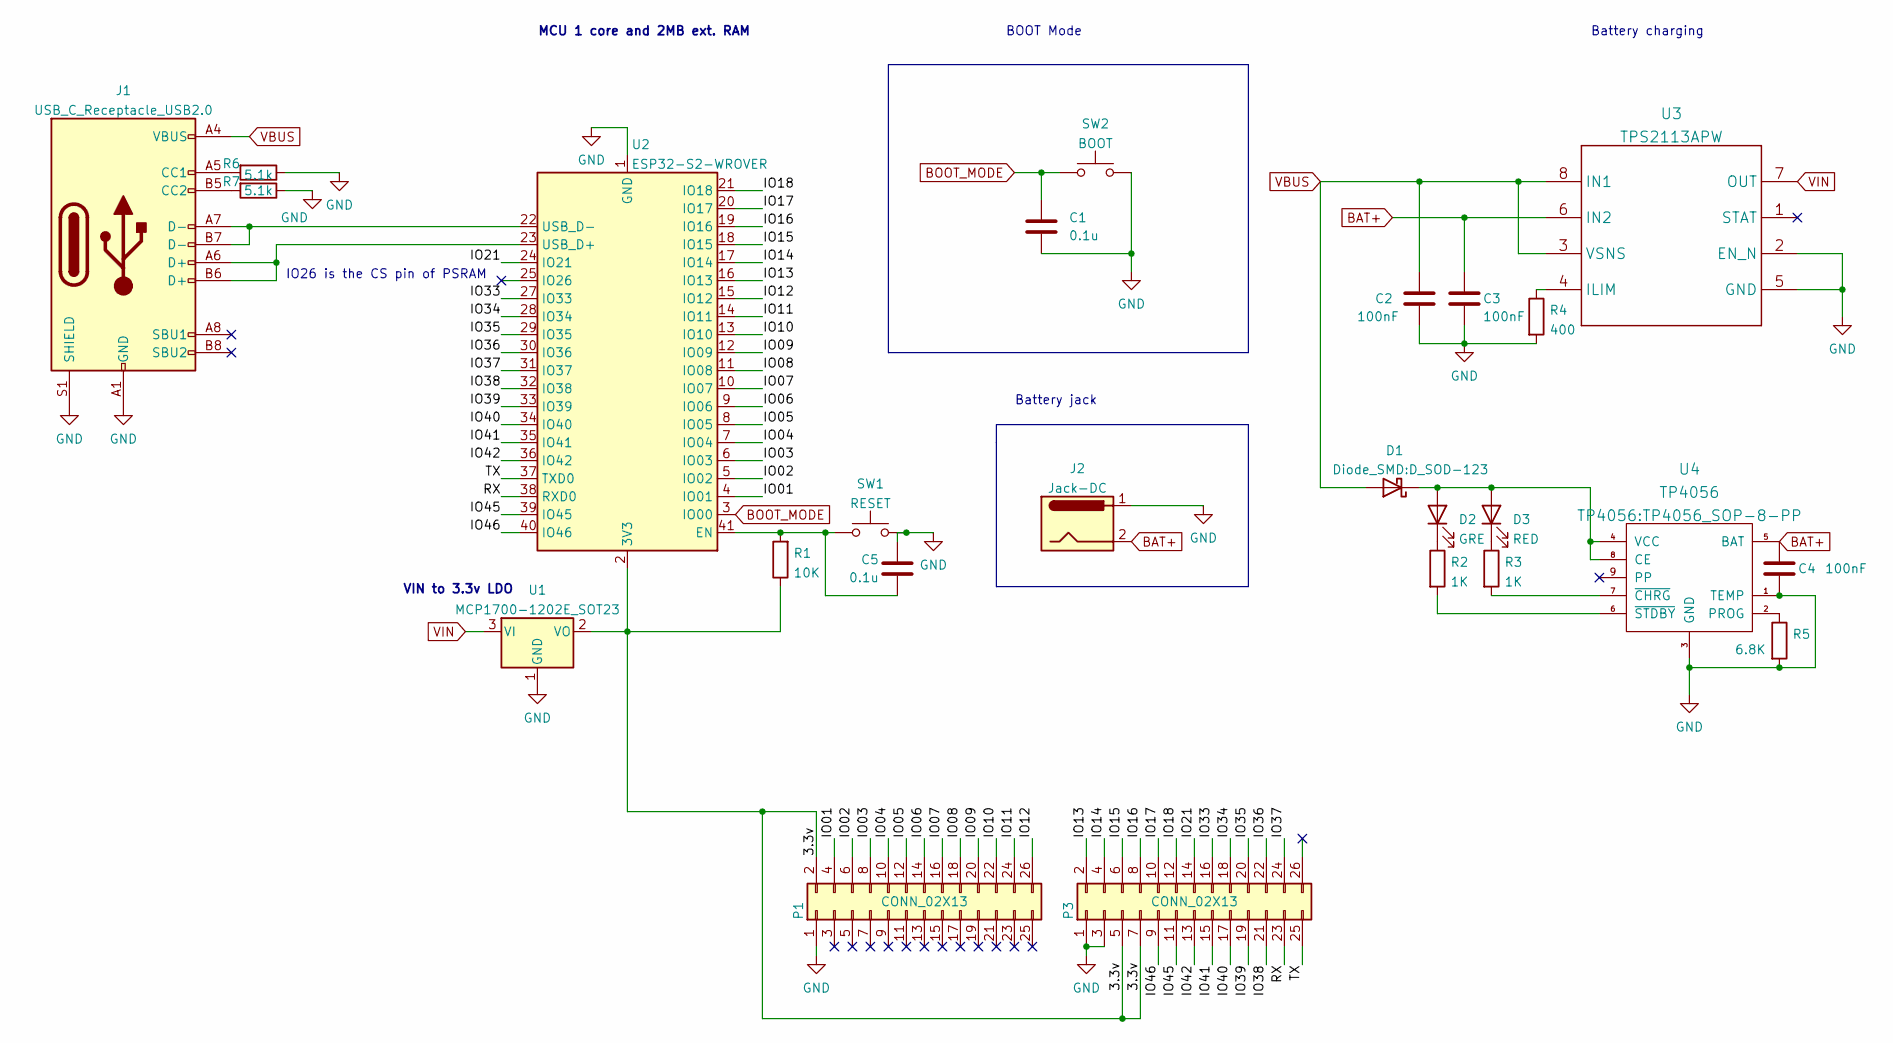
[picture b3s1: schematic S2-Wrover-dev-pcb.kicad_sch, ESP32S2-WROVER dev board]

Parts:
C1, C5: 0.1u; C_0805_2012Metric
C2, C3, C4: 100nF; C_0805_2012Metric
D1: D_Schottky; D_SOD-123; LCSC C8598
D2: GRE; LED_0805_2012Metric
D3: RED; LED_0805_2012Metric
J1: USB_C_Receptacle_USB2.0; USB_C_Receptacle_HRO_TYPE-C-31-M-12; LCSC C165948
J2: Jack-DC; JST_EH_S2B-EH_1x02_P2.50mm_Horizontal
P1, P3: CONN_02X13; PinHeader_2x13_P2.54mm_Vertical
R1: 10K; R_0603_1608Metric
R2, R3: 1K; R_0603_1608Metric
R4: 400; R_0603_1608Metric
R5: 6.8K; R_0603_1608Metric
R6, R7: 5.1k; R_0603_1608Metric
SW1: RESET; Alps_SKRK
SW2: BOOT; Alps_SKRK
U1: MCP1700-1202E_SOT23; SOT-23
U2: ESP32-S2-WROVER
U3: TPS2113APW
U4: TP4056; TP4056_SOP-8-PP

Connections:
/3.3v: P1.2, P3.5, P3.7, R1.1, U1.2 (VO), U2.2 (3V3); also elsewhere on the board
/IO01: P1.4, U2.4 (IO01); also elsewhere on the board
/IO02: P1.6, U2.5 (IO02); also elsewhere on the board
/IO03: P1.8, U2.6 (IO03); also elsewhere on the board
/IO04: P1.10, U2.7 (IO04); also elsewhere on the board
/IO05: P1.12, U2.8 (IO05); also elsewhere on the board
/IO06: P1.14, U2.9 (IO06); also elsewhere on the board
/IO07: P1.16, U2.10 (IO07); also elsewhere on the board
/IO08: P1.18, U2.11 (IO08); also elsewhere on the board
/IO09: P1.20, U2.12 (IO09); also elsewhere on the board
/IO10: P1.22, U2.13 (IO10); also elsewhere on the board
/IO11: P1.24, U2.14 (IO11); also elsewhere on the board
/IO12: P1.26, U2.15 (IO12); also elsewhere on the board
/IO13: P3.2, U2.16 (IO13)
/IO14: P3.4, U2.17 (IO14)
/IO15: P3.6, U2.18 (IO15)
/IO16: P3.8, U2.19 (IO16)
/IO17: P3.10, U2.20 (IO17)
/IO18: P3.12, U2.21 (IO18)
/IO21: P3.14, U2.24 (IO21)
/IO33: P3.16, U2.27 (IO33)
/IO34: P3.18, U2.28 (IO34)
/IO35: P3.20, U2.29 (IO35)
/IO36: P3.22, U2.30 (IO36)
/IO37: P3.24, U2.31 (IO37)
/IO38: P3.21, U2.32 (IO38)
/IO39: P3.19, U2.33 (IO39)
/IO40: P3.17, U2.34 (IO40)
/IO41: P3.15, U2.35 (IO41)
/IO42: P3.13, U2.36 (IO42)
/IO45: P3.11, U2.39 (IO45)
/IO46: P3.9, U2.40 (IO46)
/RX: P3.23, U2.38 (RXD0)
/TX: P3.25, U2.37 (TXD0)
BAT+: C3.2, C4.2, J2.2, U3.6 (IN2), U4.5 (BAT)
BOOT_MODE: C1.2, SW2.1, U2.3 (IO00)
GND: C1.1, C2.1, C3.1, C4.1, C5.1, J1.A1 (GND), J1.A12 (GND), J1.B1 (GND), J1.B12 (GND), J1.S1 (SHIELD), J2.1, P1.1, P3.1, P3.3, R4.2, R5.2, R6.1, R7.1, SW1.2, SW2.2, U1.1 (GND), U2.1 (GND), U2.26 (GND), U2.42 (GND), U2.43 (GND), U3.2 (EN_N), U3.5 (GND), U4.1 (TEMP), U4.3 (GND); also elsewhere on the board
unnamed: C5.2, R1.2, SW1.1, U2.41 (EN)
unnamed: D2.1 (K), R2.1
unnamed: D3.1 (K), R3.1
unnamed: J1.A5 (CC1), R6.2
unnamed: J1.A6 (D+), J1.B6 (D+), U2.23 (USB_D+)
unnamed: J1.A7 (D-), J1.B7 (D-), U2.22 (USB_D-)
unnamed: J1.B5 (CC2), R7.2
unnamed: R2.2, U4.6 (~STDBY)
unnamed: R3.2, U4.7 (~CHRG)
unnamed: R4.1, U3.4 (ILIM)
unnamed: R5.1, U4.2 (PROG)
VIN: U1.3 (VI), U3.7 (OUT)

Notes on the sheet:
Battery charging
Battery jack
BOOT Mode
MCU 1 core and 2MB ext. RAM
IO26 is the CS pin of PSRAM
VIN to 3.3v LDO

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
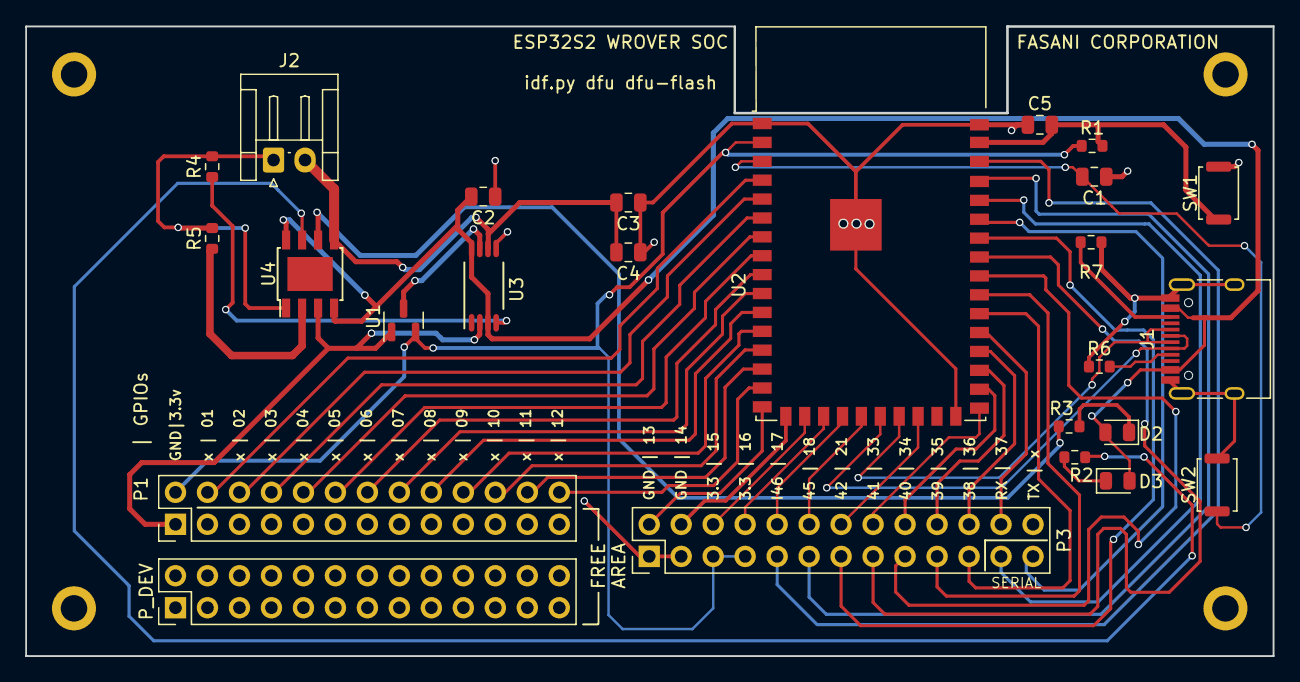
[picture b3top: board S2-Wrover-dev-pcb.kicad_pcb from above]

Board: 2 copper layers, 99.0 x 50.0 mm, 29 parts (0 on the bottom side), 50 nets.

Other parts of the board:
MK1, MK2, MK2#2, MK3: Mounting_Hole; MountingHole_3-5mm
P1   | GPIOs: CONN_02X13; PinHeader_2x13_P2.54mm_Vertical
P_DEV: CONN_02X13; PinHeader_2x13_P2.54mm_Vertical

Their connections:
/3.3v: P1 | GPIOs.2; also elsewhere on the board
/IO01: P1 | GPIOs.4; also elsewhere on the board
/IO02: P1 | GPIOs.6; also elsewhere on the board
/IO03: P1 | GPIOs.8; also elsewhere on the board
/IO04: P1 | GPIOs.10; also elsewhere on the board
/IO05: P1 | GPIOs.12; also elsewhere on the board
/IO06: P1 | GPIOs.14; also elsewhere on the board
/IO07: P1 | GPIOs.16; also elsewhere on the board
/IO08: P1 | GPIOs.18; also elsewhere on the board
/IO09: P1 | GPIOs.20; also elsewhere on the board
/IO10: P1 | GPIOs.22; also elsewhere on the board
/IO11: P1 | GPIOs.24; also elsewhere on the board
/IO12: P1 | GPIOs.26; also elsewhere on the board
GND: P1 | GPIOs.1; also elsewhere on the board

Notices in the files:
parts and their libraries:
Copyright 2016 Accelerated Designs. All rights reserved.
